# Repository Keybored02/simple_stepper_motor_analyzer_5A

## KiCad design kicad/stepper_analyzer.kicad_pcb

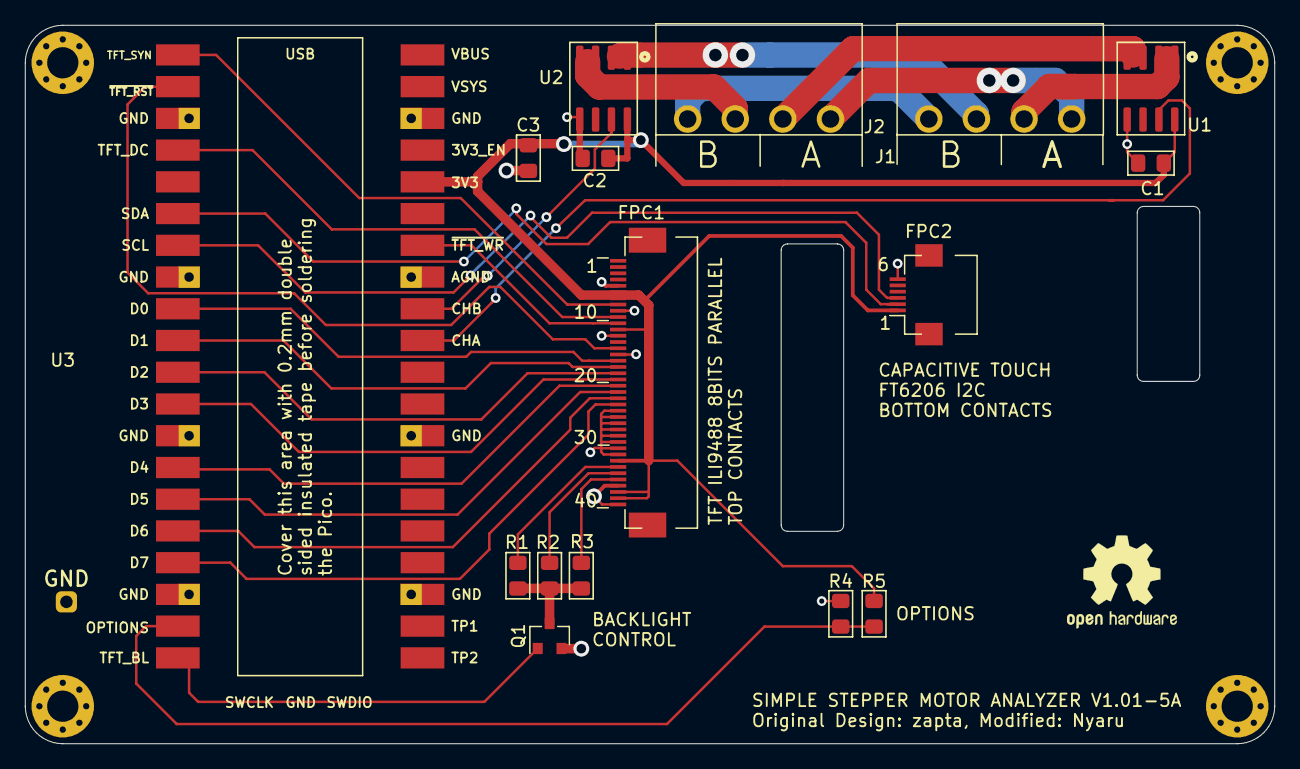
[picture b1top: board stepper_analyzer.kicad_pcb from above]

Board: 2 copper layers, 100.0 x 57.5 mm, 23 parts (1 on the bottom side), 30 nets.

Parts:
C1, C2: 0.1u; C_0805_2012Metric_Pad1.15x1.40mm_HandSolder
C3: 10u; C_0805_2012Metric_Pad1.15x1.40mm_HandSolder
FPC1: Connector_Conn_01x40_Female; JUSHUO-AFC07-S40ECC-00_40P_05mm_flipped
FPC2: FPC connector, 6 pins, 0.5mm, BOTTOM contacts; JUSHUO-AFC01-S06FCC-00_6p_05mm
H1, H2, H3, H4: MountingHole; MountingHole_2.5mm_Pad_Via
J1, J2: Connector_Conn_01x04_Male; Connector_green_big
LOGO1: Logo_Open_Hardware_Small; OSHW-Logo2_9.8x8mm_SilkScreen
M1: Motor; null_footprint
Q1: AO3400A; SOT-23
R1, R2, R3: 8R2; R_0805_2012Metric_Pad1.15x1.40mm_HandSolder
R4, R5: DNP; R_0805_2012Metric_Pad1.15x1.40mm_HandSolder_no_3d
TP3: TestPoint; testpoint_double_side
U1, U2: ACS70331EOLCTR-2P5B3; SOIC-8_3.9x4.9mm_P1.27mm
U3: Pico; Pico_smd_dedicated

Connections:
+3V3: C1.2, C2.2, C3.2, FPC1.6, FPC1.7, FPC1.12, FPC1.33, FPC1.38, FPC1.39, FPC2.1, R5.2, U1.8, U2.8, U3.36
/CHA: U1.7, U3.31
/CHB: U2.7, U3.32
/D0: FPC1.17, U3.9
/D1: FPC1.18, U3.10
/D2: FPC1.19, U3.11
/D3: FPC1.20, U3.12
/D4: FPC1.21, U3.14
/D5: FPC1.22, U3.15
/D6: FPC1.23, U3.16
/D7: FPC1.24, U3.17
/OPTIONS: R4.1, R5.1, U3.19
/SCL: FPC2.3, U3.7
/SDA: FPC2.2, U3.6
/TFT_BL: Q1.1, U3.20
/TFT_DC: FPC1.10, U3.4
/TFT_SYN: FPC1.8, U3.1
/~TFT_RST: FPC1.15, U3.2
/~TFT_WR: FPC1.11, U3.34
GND: C1.1, C2.1, C3.1, FPC1.5, FPC1.9, FPC1.13, FPC1.16, FPC1.25, FPC1.26, FPC1.27, FPC1.28, FPC1.29, FPC1.30, FPC1.31, FPC1.32, FPC1.37, FPC1.40, FPC2.6, Q1.2, R4.2, TP3.1, U1.5, U2.5, U3.3, U3.8, U3.13, U3.18, U3.23, U3.28, U3.33, U3.38
unnamed: FPC1.34, R1.2
unnamed: FPC1.35, R2.2
unnamed: FPC1.36, R3.2
unnamed: J1.1, J2.1
unnamed: J1.2, U1.1, U1.2
unnamed: J1.3, U2.1, U2.2
unnamed: J1.4, J2.4
unnamed: J2.2, U1.3, U1.4
unnamed: J2.3, U2.3, U2.4
unnamed: Q1.3, R1.1, R2.1, R3.1

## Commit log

2022-06-30 Add avg and peak values to current histogram page
2022-08-10 change graph range to +-5A
2022-08-10 add simplified RMS calculation
2022-09-06 add 3d case model
2022-09-06 update to current kicad model (for CC6920BSO)
2022-09-28 fix dimensions of case top model
2023-10-10 updated platform io for future builds
    old platform repo was deleted, updated with duplicated copy.
